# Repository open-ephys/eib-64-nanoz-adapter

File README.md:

## EIB-64 NanoZ Adapter

Adapter to interface [Open Ephys 64ch EIB](https://github.com/open-ephys/eib-64) with the popular nanoZ electrode impedance tester and plating device.

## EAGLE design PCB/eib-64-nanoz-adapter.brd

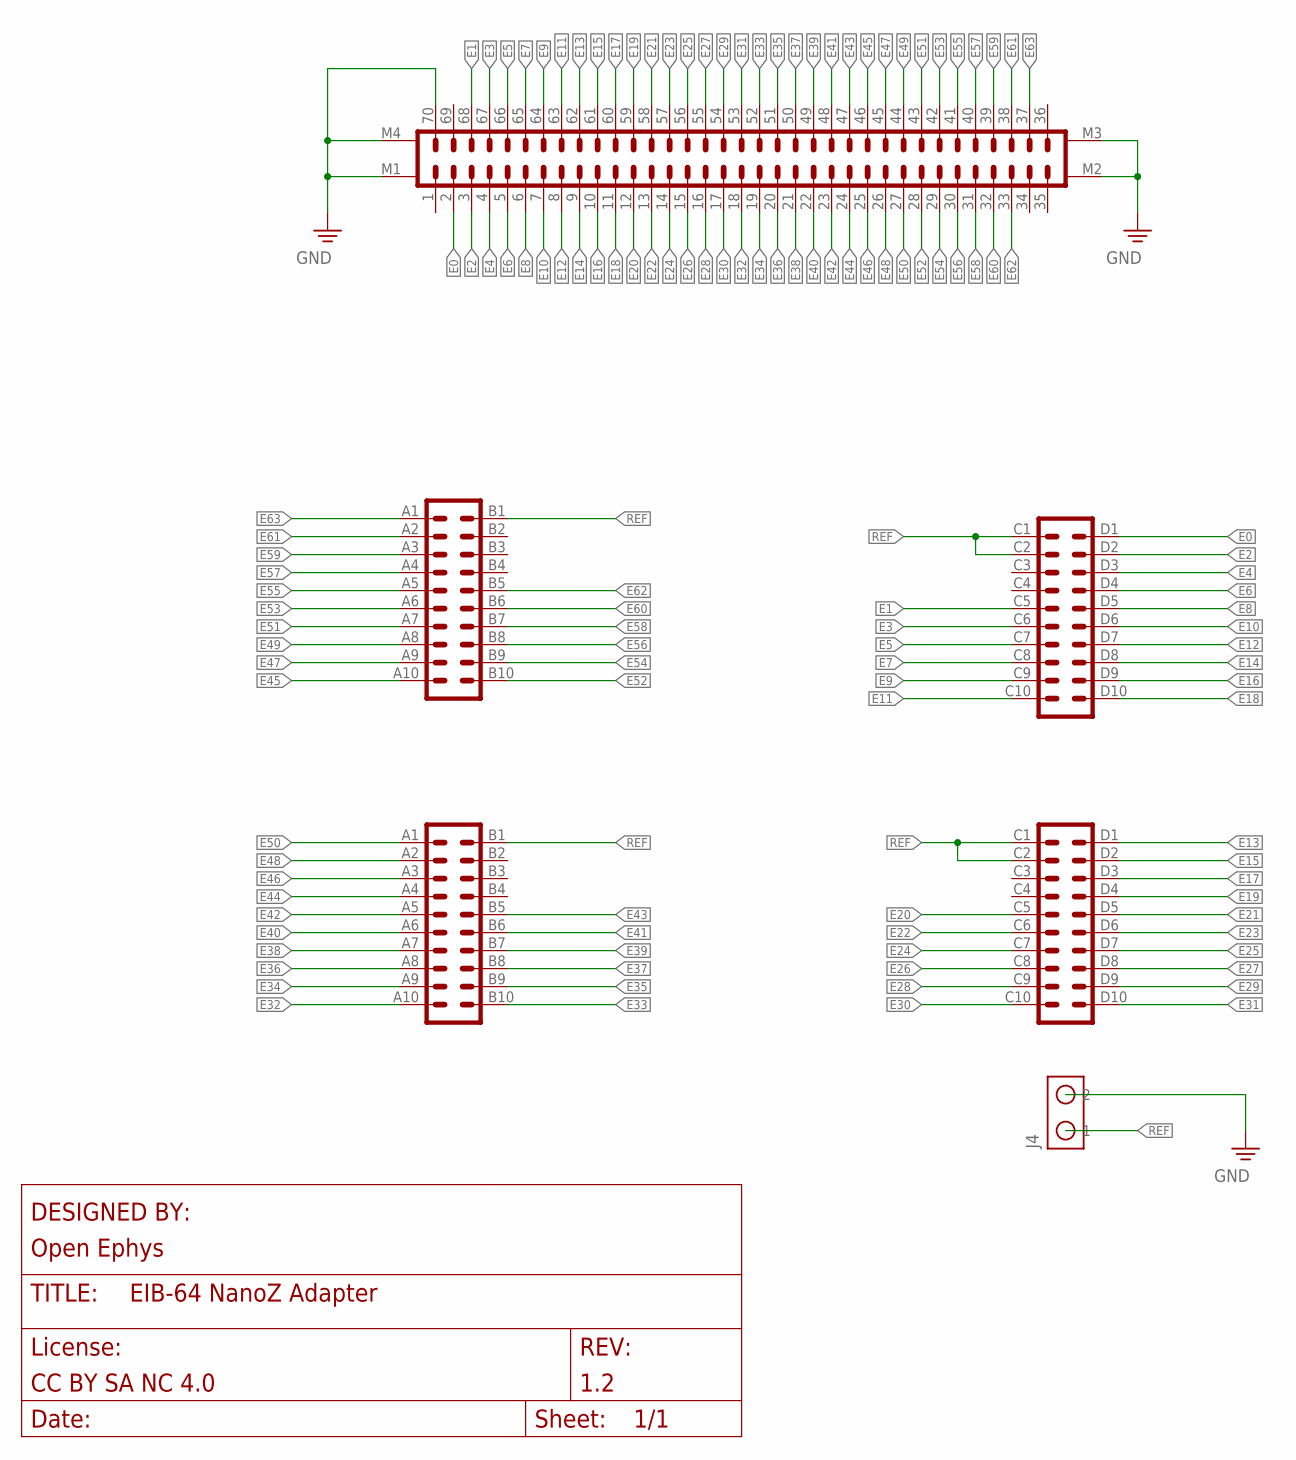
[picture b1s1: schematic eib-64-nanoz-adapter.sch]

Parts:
J1: DF40-REC; DF40-70HEAD
J2, J3: PINHD-4X10_MOLC-THRU; MOLC-110-11-S-Q
J4: SCREW2

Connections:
E0: J1.2, J2.D1 (20)
E1: J1.68, J2.C5 (5)
E2: J1.3, J2.D2 (19)
E3: J1.67, J2.C6 (6)
E4: J1.4, J2.D3 (18)
E5: J1.66, J2.C7 (7)
E6: J1.5, J2.D4 (17)
E7: J1.65, J2.C8 (8)
E8: J1.6, J2.D5 (16)
E9: J1.64, J2.C9 (9)
E10: J1.7, J2.D6 (15)
E11: J1.63, J2.C10 (10)
E12: J1.8, J2.D7 (14)
E13: J1.62, J3.D1 (20)
E14: J1.9, J2.D8 (13)
E15: J1.61, J3.D2 (19)
E16: J1.10, J2.D9 (12)
E17: J1.60, J3.D3 (18)
E18: J1.11, J2.D10 (11)
E19: J1.59, J3.D4 (17)
E20: J1.12, J3.C5 (5)
E21: J1.58, J3.D5 (16)
E22: J1.13, J3.C6 (6)
E23: J1.57, J3.D6 (15)
E24: J1.14, J3.C7 (7)
E25: J1.56, J3.D7 (14)
E26: J1.15, J3.C8 (8)
E27: J1.55, J3.D8 (13)
E28: J1.16, J3.C9 (9)
E29: J1.54, J3.D9 (12)
E30: J1.17, J3.C10 (10)
E31: J1.53, J3.D10 (11)
E32: J1.18, J3.A10 (10)
E33: J1.52, J3.B10 (11)
E34: J1.19, J3.A9 (9)
E35: J1.51, J3.B9 (12)
E36: J1.20, J3.A8 (8)
E37: J1.50, J3.B8 (13)
E38: J1.21, J3.A7 (7)
E39: J1.49, J3.B7 (14)
E40: J1.22, J3.A6 (6)
E41: J1.48, J3.B6 (15)
E42: J1.23, J3.A5 (5)
E43: J1.47, J3.B5 (16)
E44: J1.24, J3.A4 (4)
E45: J1.46, J2.A10 (10)
E46: J1.25, J3.A3 (3)
E47: J1.45, J2.A9 (9)
E48: J1.26, J3.A2 (2)
E49: J1.44, J2.A8 (8)
E50: J1.27, J3.A1 (1)
E51: J1.43, J2.A7 (7)
E52: J1.28, J2.B10 (11)
E53: J1.42, J2.A6 (6)
E54: J1.29, J2.B9 (12)
E55: J1.41, J2.A5 (5)
E56: J1.30, J2.B8 (13)
E57: J1.40, J2.A4 (4)
E58: J1.31, J2.B7 (14)
E59: J1.39, J2.A3 (3)
E60: J1.32, J2.B6 (15)
E61: J1.38, J2.A2 (2)
E62: J1.33, J2.B5 (16)
E63: J1.37, J2.A1 (1)
GND: J1.70, J1.M1, J1.M2, J1.M3, J1.M4, J4.P$2 (2)
REF: J2.B1 (20), J2.C1 (1), J2.C2 (2), J3.B1 (20), J3.C1 (1), J3.C2 (2), J4.P$1 (1)

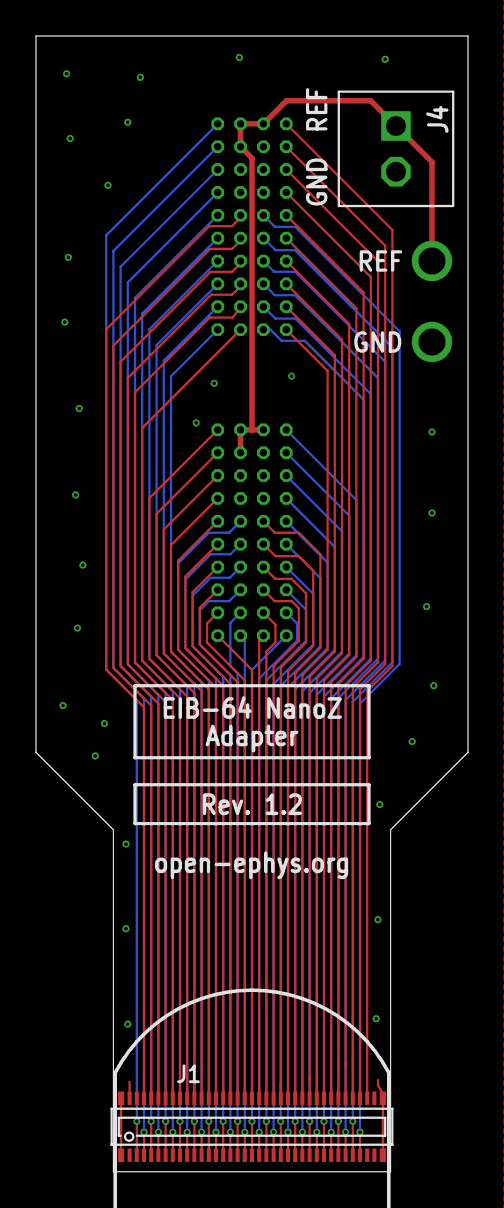
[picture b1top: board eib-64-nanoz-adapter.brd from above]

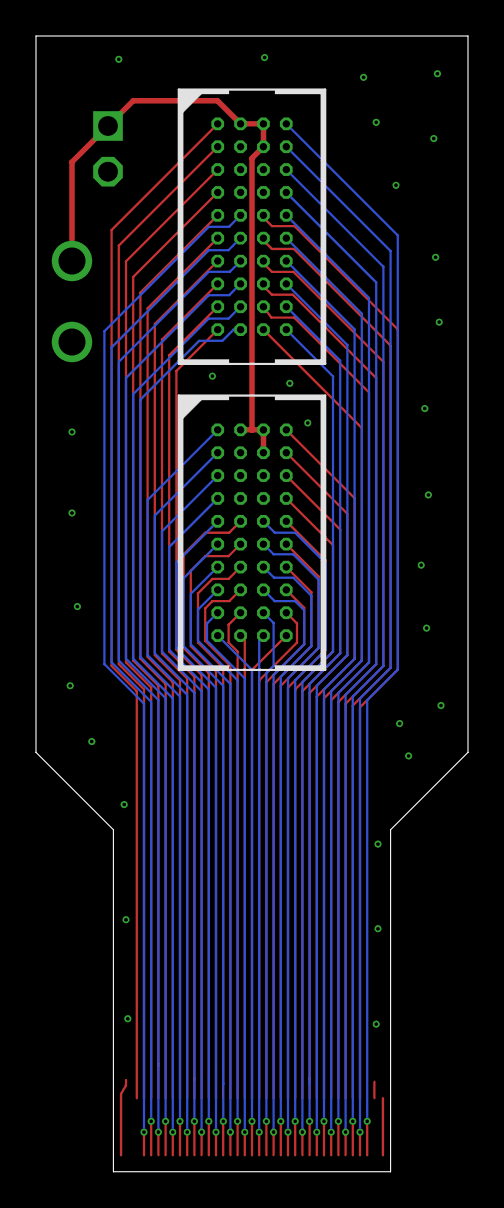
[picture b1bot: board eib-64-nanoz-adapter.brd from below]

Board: 4 copper layers, 24.0 x 63.1 mm, 4 parts (2 on the bottom side), 66 nets.

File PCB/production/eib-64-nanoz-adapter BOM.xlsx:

Qty | OEPS PN | Schematic Name | MPN
1 | OEPS070068 | J1 | DF40C-70DP-0.4V(51)
2 | OEPS070132 | J2, J3 | MOLC-110-11-S-Q
1 | OEPS070133 | J4 | OSTVN02A150

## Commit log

2025-09-24 Created README.md
2025-09-24 Added LICENSE
2025-09-24 Added PCB and schematic
    Fix #2
2025-09-24 Added .gitignore for Eagle CAD
2025-09-24 Added BOM
2025-09-24 Added production files
2025-09-24 Added .ini files to .gitignore
2025-09-24 Change licence to CC BY SA NC 4.0
2025-09-25 Removed LICENSE file

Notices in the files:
PCB/eib-64-nanoz-adapter.sch:
LICENSE: CC BY SA NC 4.0
